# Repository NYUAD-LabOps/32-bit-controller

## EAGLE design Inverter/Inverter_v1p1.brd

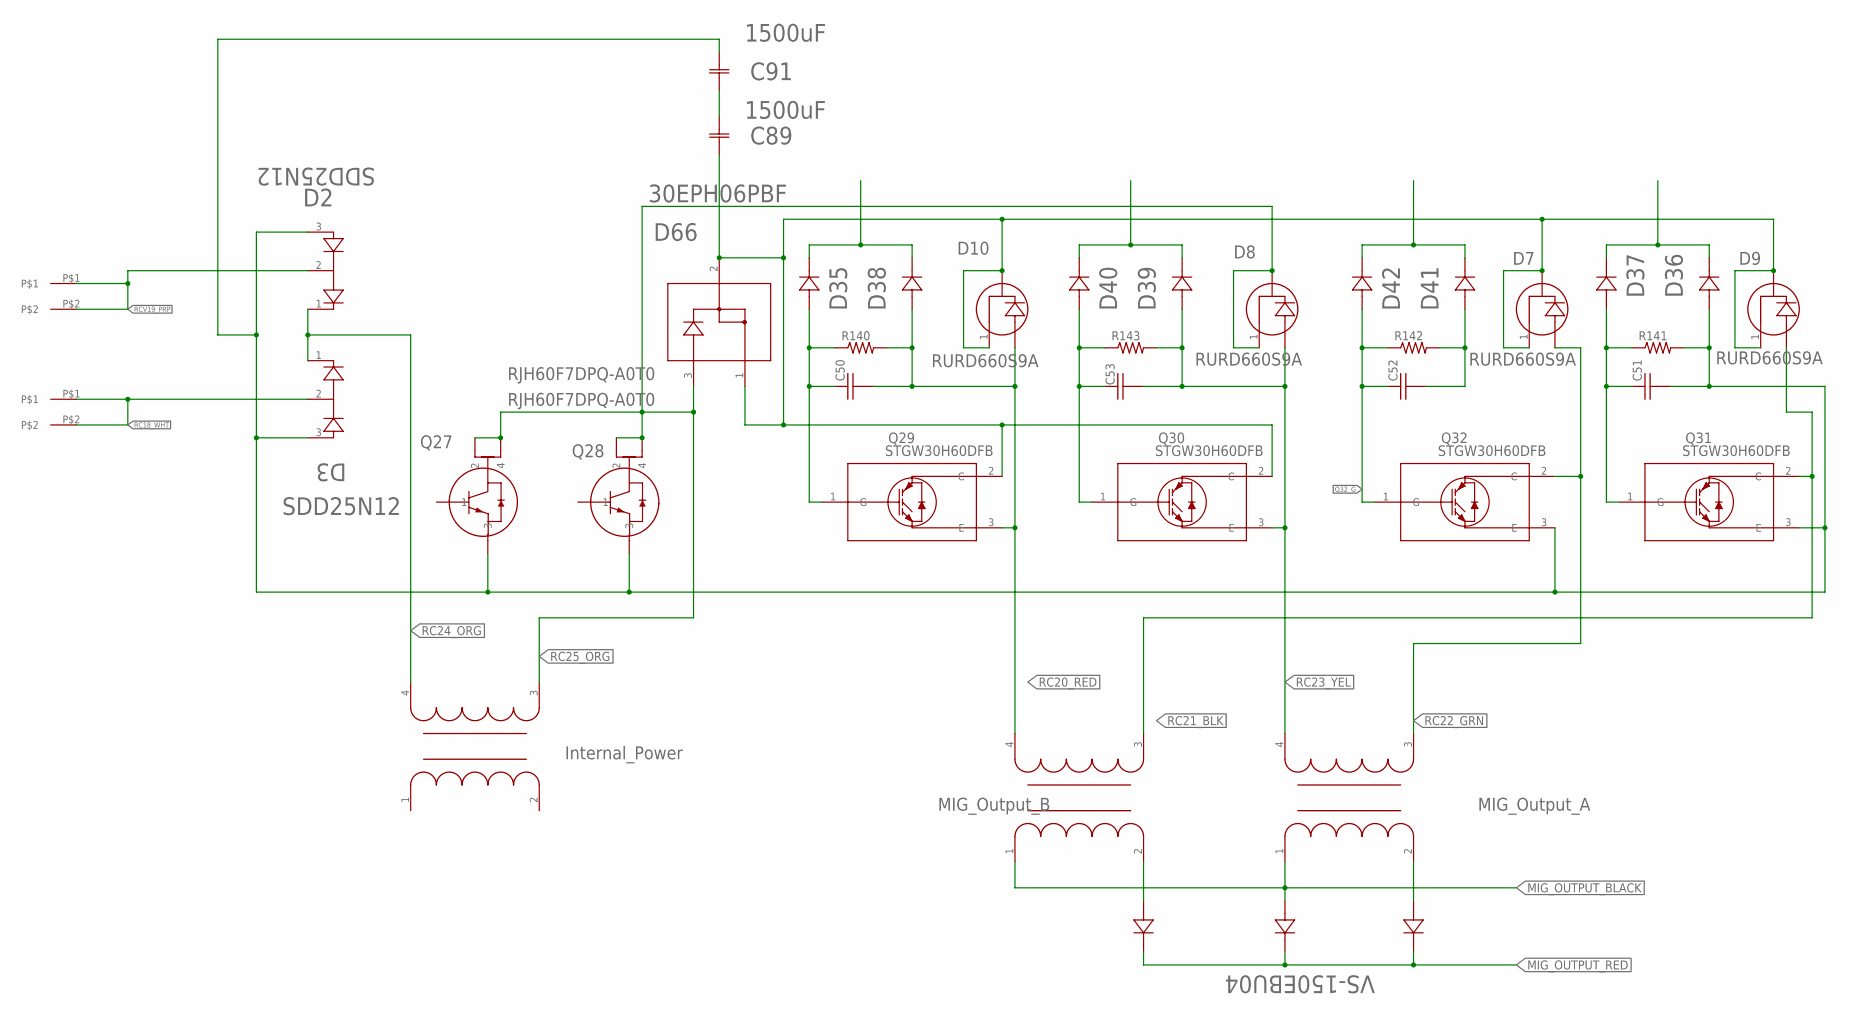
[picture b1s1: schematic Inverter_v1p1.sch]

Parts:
C50, C51, C52, C53: C_0805; 0805
C89, C91: 1500uF; CAP_SLP152M250H9P3_CND
D2, D3: SDD25N12; TO-247AD
D7, D8, D9, D10: RURD660S9A; TO-252
D35, D36, D37, D39, D40, D41, D42: SMAZ18-13-FSMA_DIO-M; SMA_DIO-M
D38: ZJF_638; SMA_DIO-M
D66: 30EPH06PBF; TO-247AC_MOD_VIS
J2, J3: 2-pos; 2_3.81MM_PITCH
Q27, Q28: RJH60F7DPQ-A0T0; TO-247A_REN
Q29, Q30, Q31, Q32: STGW30H60DFB; TO-247_STM
R140, R141, R142, R143: R_0805; 0805
U$1, U$2, U$3: GENERIC_TRANSFORMER
U$4, U$5, U$6: VS-150EBU04; POWER_TAB

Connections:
D66_1: C89.2, D7.1 (C1), D7.3 (C2), D9.1 (C1), D9.3 (C2), D10.1 (C1), D10.3 (C2), D66.1, D66.2, Q29.2 (C), Q30.2 (C)
MIG_OUTPUT_BLACK: U$1.1, U$2.1, U$5.2
MIG_OUTPUT_RED: U$4.1, U$5.1, U$6.1
unnamed: U$1.2, U$4.2
unnamed: C50.1, D35.2, Q29.1 (G), R140.1
unnamed: D39.1, D40.1
unnamed: U$2.2, U$6.2
unnamed: C89.1, C91.2
unnamed: D35.1, D38.1
unnamed: C53.1, D40.2, Q30.1 (G), R143.1
unnamed: C51.1, D37.2, Q31.1 (G), R141.1
unnamed: C52.2, D41.2, R142.2
unnamed: D41.1, D42.1
unnamed: C51.2, C91.1, D2.3, D3.3, D36.2, Q27.3, Q28.3, Q31.3 (E), Q32.3 (E), R141.2
unnamed: D36.1, D37.1
Q32_G: C52.1, D42.2, Q32.1 (G), R142.1
RC18_WHT: D3.2, J3.P$1, J3.P$2
RC20_RED: C50.2, D10.2 (A), D38.2, Q29.3 (E), R140.2, U$1.4
RC21_BLK: D9.2 (A), Q31.2 (C), U$1.3
RC22_GRN: D7.2 (A), Q32.2 (C), U$2.3
RC23_YEL: C53.2, D8.2 (A), D39.2, Q30.3 (E), R143.2, U$2.4
RC24_ORG: D2.1, D3.1, U$3.4
RC25_ORG: D8.1 (C1), D8.3 (C2), D66.3, Q27.2, Q27.4, Q28.2, Q28.4, U$3.3
RCV19_PRP: D2.2, J2.P$1, J2.P$2

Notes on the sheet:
MIG_Output_A
Internal_Power
MIG_Output_B

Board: 2 copper layers, 39 parts (0 on the bottom side), 24 nets, no tracks yet.

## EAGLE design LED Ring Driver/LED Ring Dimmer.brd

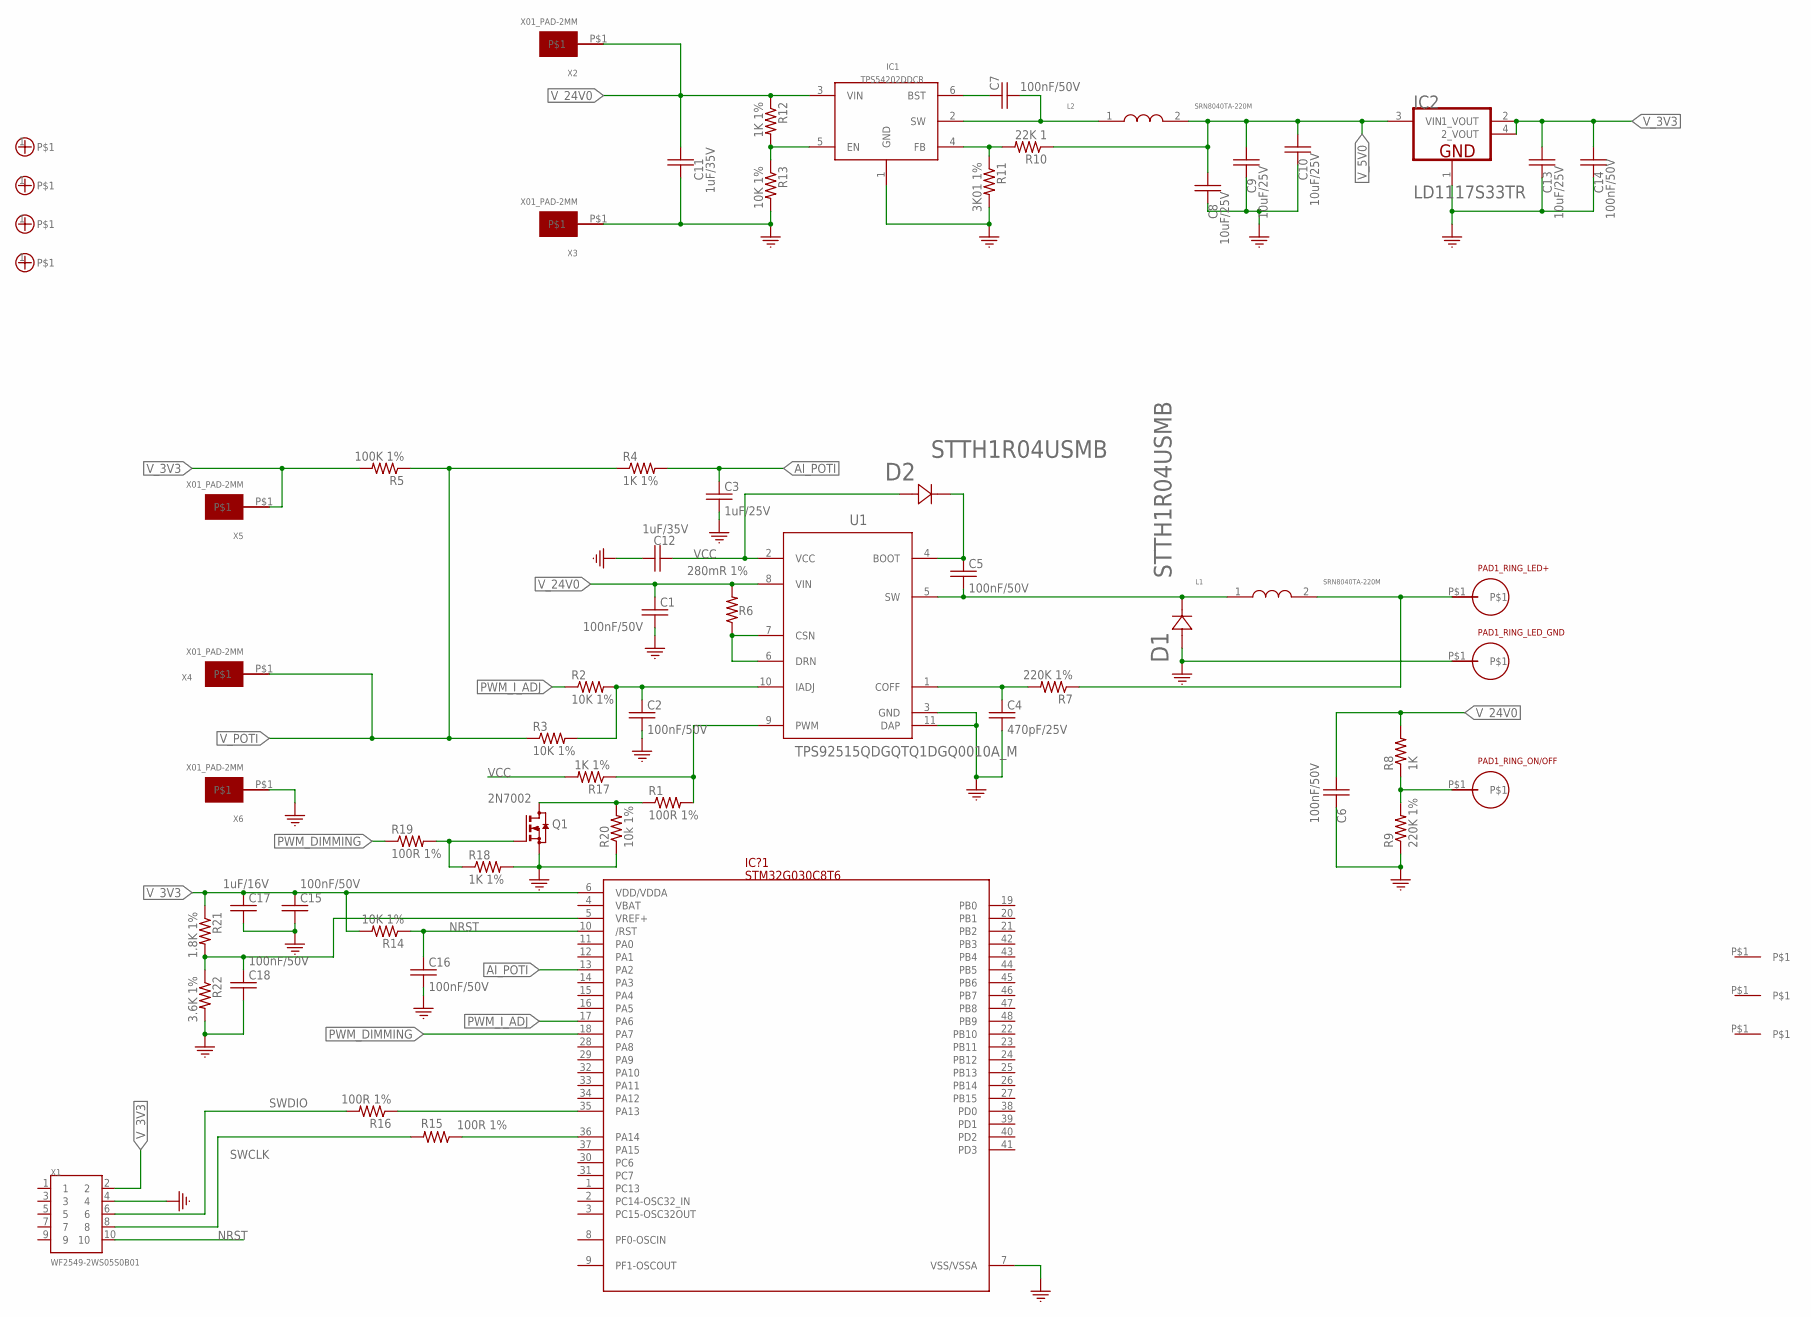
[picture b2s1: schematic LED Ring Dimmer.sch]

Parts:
C1, C2, C5, C6, C7, C14, C15, C16, C18: 100nF/50V; EIA0603
C3: 1uF/25V; EIA0603
C4: 470pF/25V; EIA0603
C8, C9, C10, C13: 10uF/25V; EIA0603
C11, C12: 1uF/35V; EIA0603
C17: 1uF/16V; EIA0603
D1, D2: STTH1R04USMB; SMB
FID1, FID2, FID3: FIDUCIAL
IC1: TPS54202DDCR; SOT23-6
IC2: LD1117S33TR; SOT223_LD1117S33TR
IC?1: STM32G030C8T6; LQFP48
L1, L2: SRN8040TA-220M
M1, M2, M3, M4: M_HOLE_3M; PCB_SCREW_M3_POWER
PAD1_RING_LED+, PAD1_RING_LED_GND, PAD1_RING_ON/OFF: THT_PAD_5MM; THT_PAD_D5.0
Q1: 2N7002; SOT23
R1, R15, R16, R19: 100R 1%; EIA0603
R2, R3, R13, R14: 10K 1%; EIA0603
R4, R12, R17, R18: 1K 1%; EIA0603
R5: 100K 1%; EIA0603
R6: 280mR 1%; EIA1206
R7, R9: 220K 1%; EIA0603
R8: 1K; EIA0603
R10: 22K 1; EIA0603
R11: 3K01 1%; EIA0603
R20: 10k 1%; EIA0603
R21: 1.8K 1%; EIA0603
R22: 3.6K 1%; EIA0603
U1: TPS92515QDGQTQ1DGQ0010A_M; DGQ0010A_M
X1: WF2549-2WS05S0B01; X10_100MIL_2XROW_VERT
X2, X3, X4, X5, X6: X01_PAD-2MM

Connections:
AI_POTI: C3.1, IC?1.13 (PA2), R4.2
GND: C1.2, C2.2, C3.2, C4.2, C6.2, C8.2, C9.2, C10.2, C11.2, C12.1, C13.2, C14.2, C15.2, C16.2, C17.2, C18.2, D1.A, IC1.1 (GND), IC2.1 (GND), IC?1.7 (VSS/VSSA), PAD1_RING_LED_GND.P$1, Q1.2 (S), R9.1, R11.2, R13.2, R18.2, R20.1, R22.2, U1.3 (GND), U1.11 (DAP), X1.4, X3.P$1, X6.P$1
unnamed: C1.1, R6.2, U1.8 (VIN)
unnamed: C5.2, D1.K (C), L1.1, U1.5 (SW)
unnamed: R6.1, U1.6 (DRN), U1.7 (CSN)
unnamed: C2.1, R2.2, R3.2, U1.10 (IADJ)
unnamed: C4.1, R7.2, U1.1 (COFF)
unnamed: R1.2, R17.1, U1.9 (PWM)
unnamed: L1.2, PAD1_RING_LED+.P$1, R7.1
unnamed: C5.1, D2.K (C), U1.4 (BOOT)
unnamed: PAD1_RING_ON/OFF.P$1, R8.1, R9.2
unnamed: C7.1, IC1.6 (BST)
unnamed: C7.2, IC1.2 (SW), L2.1
unnamed: IC1.4 (FB), R10.2, R11.1
unnamed: Q1.3 (D), R1.1, R20.2
unnamed: IC1.5 (EN), R12.2, R13.1
unnamed: Q1.1 (G), R18.1, R19.2
unnamed: C18.1, IC?1.5 (VREF+), R21.2, R22.1
unnamed: IC?1.35 (PA13), R16.1
unnamed: IC?1.36 (PA14), R15.1
NRST: C16.1, IC?1.10 (/RST), R14.1, X1.10
PWM_DIMMING: IC?1.18 (PA7), R19.1
PWM_I_ADJ: IC?1.17 (PA6), R2.1
SWCLK: R15.2, X1.8
SWDIO: R16.2, X1.6
VCC: C12.2, D2.A, R17.2, U1.2 (VCC)
V_3V3: C13.1, C14.1, C15.1, C17.1, IC2.2 (1_VOUT), IC2.4 (2_VOUT), IC?1.6 (VDD/VDDA), R5.2, R14.2, R21.1, X1.2, X5.P$1
V_5V0: C8.1, C9.1, C10.1, IC2.3 (VIN), L2.2, R10.1
V_24V0: C6.1, C11.1, IC1.3 (VIN), R8.2, R12.1, X2.P$1
V_POTI: R3.1, R4.1, R5.1, X4.P$1

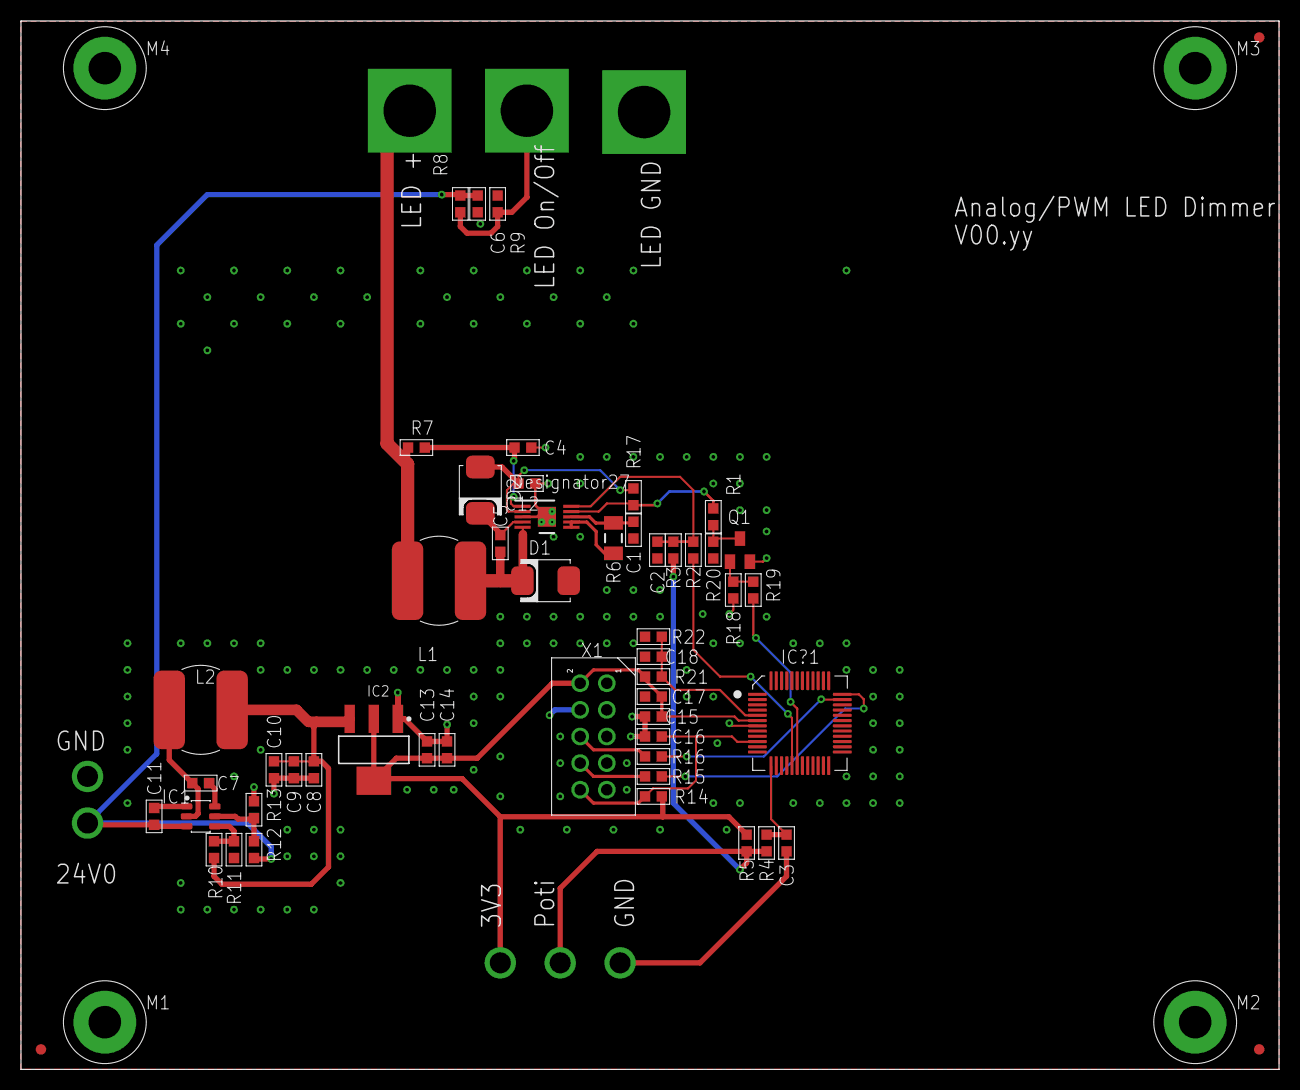
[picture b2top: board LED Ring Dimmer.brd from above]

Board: 2 copper layers, 120.0 x 100.0 mm, 65 parts (0 on the bottom side), 30 nets.

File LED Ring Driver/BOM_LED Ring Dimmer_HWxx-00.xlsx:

Qty | Value | Device | Package | Parts | DESCRIPTION | MFN | MFR | PART_VALUE
1 |  | C_0603EIA0603 | EIA0603 | C3
3 |  | R_0603 | EIA0603 | R2, R3, R7 |  | Open Source 0603
1 | 1.8K 1% | R_0603 | EIA0603 | R21 |  | Open Source 0603
1 | 100K 1% | R_0603 | EIA0603 | R5 |  | Open Source 0603
4 | 100R 1% | R_0603 | EIA0603 | R1, R15, R16, R19 |  | Open Source 0603
10 | 100nF/50V | C_0603EIA0603 | EIA0603 | C1, C2, C4, C5, C6, C7, C14, C15, C16, C18
2 | 10K 1% | R_0603 | EIA0603 | R13, R14 |  | Open Source 0603
1 | 10k 1% | R_0603 | EIA0603 | R20 |  | Open Source 0603
4 | 10uF/25V | C_0603EIA0603 | EIA0603 | C8, C9, C10, C13
1 | 1K | R_0603 | EIA0603 | R8 |  | Open Source 0603
4 | 1K 1% | R_0603 | EIA0603 | R4, R12, R17, R18 |  | Open Source 0603
1 | 1uF/16V | C_0603EIA0603 | EIA0603 | C17
2 | 1uF/35V | C_0603EIA0603 | EIA0603 | C11, C12
1 | 220K 1% | R_0603 | EIA0603 | R9 |  | Open Source 0603
1 | 22K 1 | R_0603 | EIA0603 | R10 |  | Open Source 0603
1 | 280mR 1% | R_1206EIA1206 | EIA1206 | R6 |  | Open Source R1206
1 | 2N7002 | 2N7002 | SOT23 | Q1 | NMOSFET, 500mA, 60V, Vth 2.5V | 2N7002 | Diodes, Guangdong Hotetech,NXP | NMOSFET
1 | 3.6K 1% | R_0603 | EIA0603 | R22 |  | Open Source 0603
1 | 3K01 1% | R_0603 | EIA0603 | R11 |  | Open Source 0603
3 | FIDUCIAL | FIDUCIAL | FIDUCIAL | FID1, FID2, FID3
1 | LD1117S33TR | LD1117S33TR | SOT223_LD1117S33TR | IC2 | LDO,Fixed 15V 3.3V 1.3V @ 800mA SOT-223 | LD1117S33TR | STmicro, Diodes, TI, | xx1117x33xx
4 | M_HOLE_3M | M_HOLE_3M | PCB_SCREW_M3_POWER | M1, M2, M3, M4
2 | SRN8040TA-220M | SRN8040TA-220M | SRN8040TA-220M | L1, L2 | FIXED IND 22UH 2.9A SMD, 73m-Ohm, Bourns | SRN8040TA-220M | Bourns | 22uH/2.9A
1 | STM32G030C8T6 | STM32G030C8T6 | LQFP48 | IC?1
2 | STTH1R04USMB | STTH1R04USMB | SMB | D1, D2 | 1A, 400V, SMB, Fast Recovery | STTH1R04U |  | STTH1R04U
3 | THT_PAD_5MM | THT_PAD_5MM | THT_PAD_D5.0 | PAD1_RING_LED+, PAD1_RING_LED_GND, PAD1_RING_ON/OFF
1 | TPS54202DDCR | TPS54202DDCR | SOT23-6 | IC1 | 2A 28V SOT-23-6 Sync Buck | TPS54202DDCR | Texas Instruments | TPS54202
1 | TPS92515QDGQTQ1DGQ0010A_M | TPS92515QDGQTQ1DGQ0010A_M | DGQ0010A_M | U1 | LED Driver 2A, 42V, Buck, Analog and PWM Dimming,MSOP-PowerPad-10 | TPS92515QDGQTQ1 | Texas Instruments | TPS92515
1 | WF2549-2WS05S0B01 | WF2549-2WS05S0B01 | X10_100MIL_2XROW_VERT | X1 | X10, 10 Pins, Header, Pitch 2.54 wire to board 2xrows, THT | WF2549-2WS05S0B01 | WCON
5 | X01_PAD-2MM | X01_PAD-2MM | X01_PAD-2MM | X2, X3, X4, X5, X6

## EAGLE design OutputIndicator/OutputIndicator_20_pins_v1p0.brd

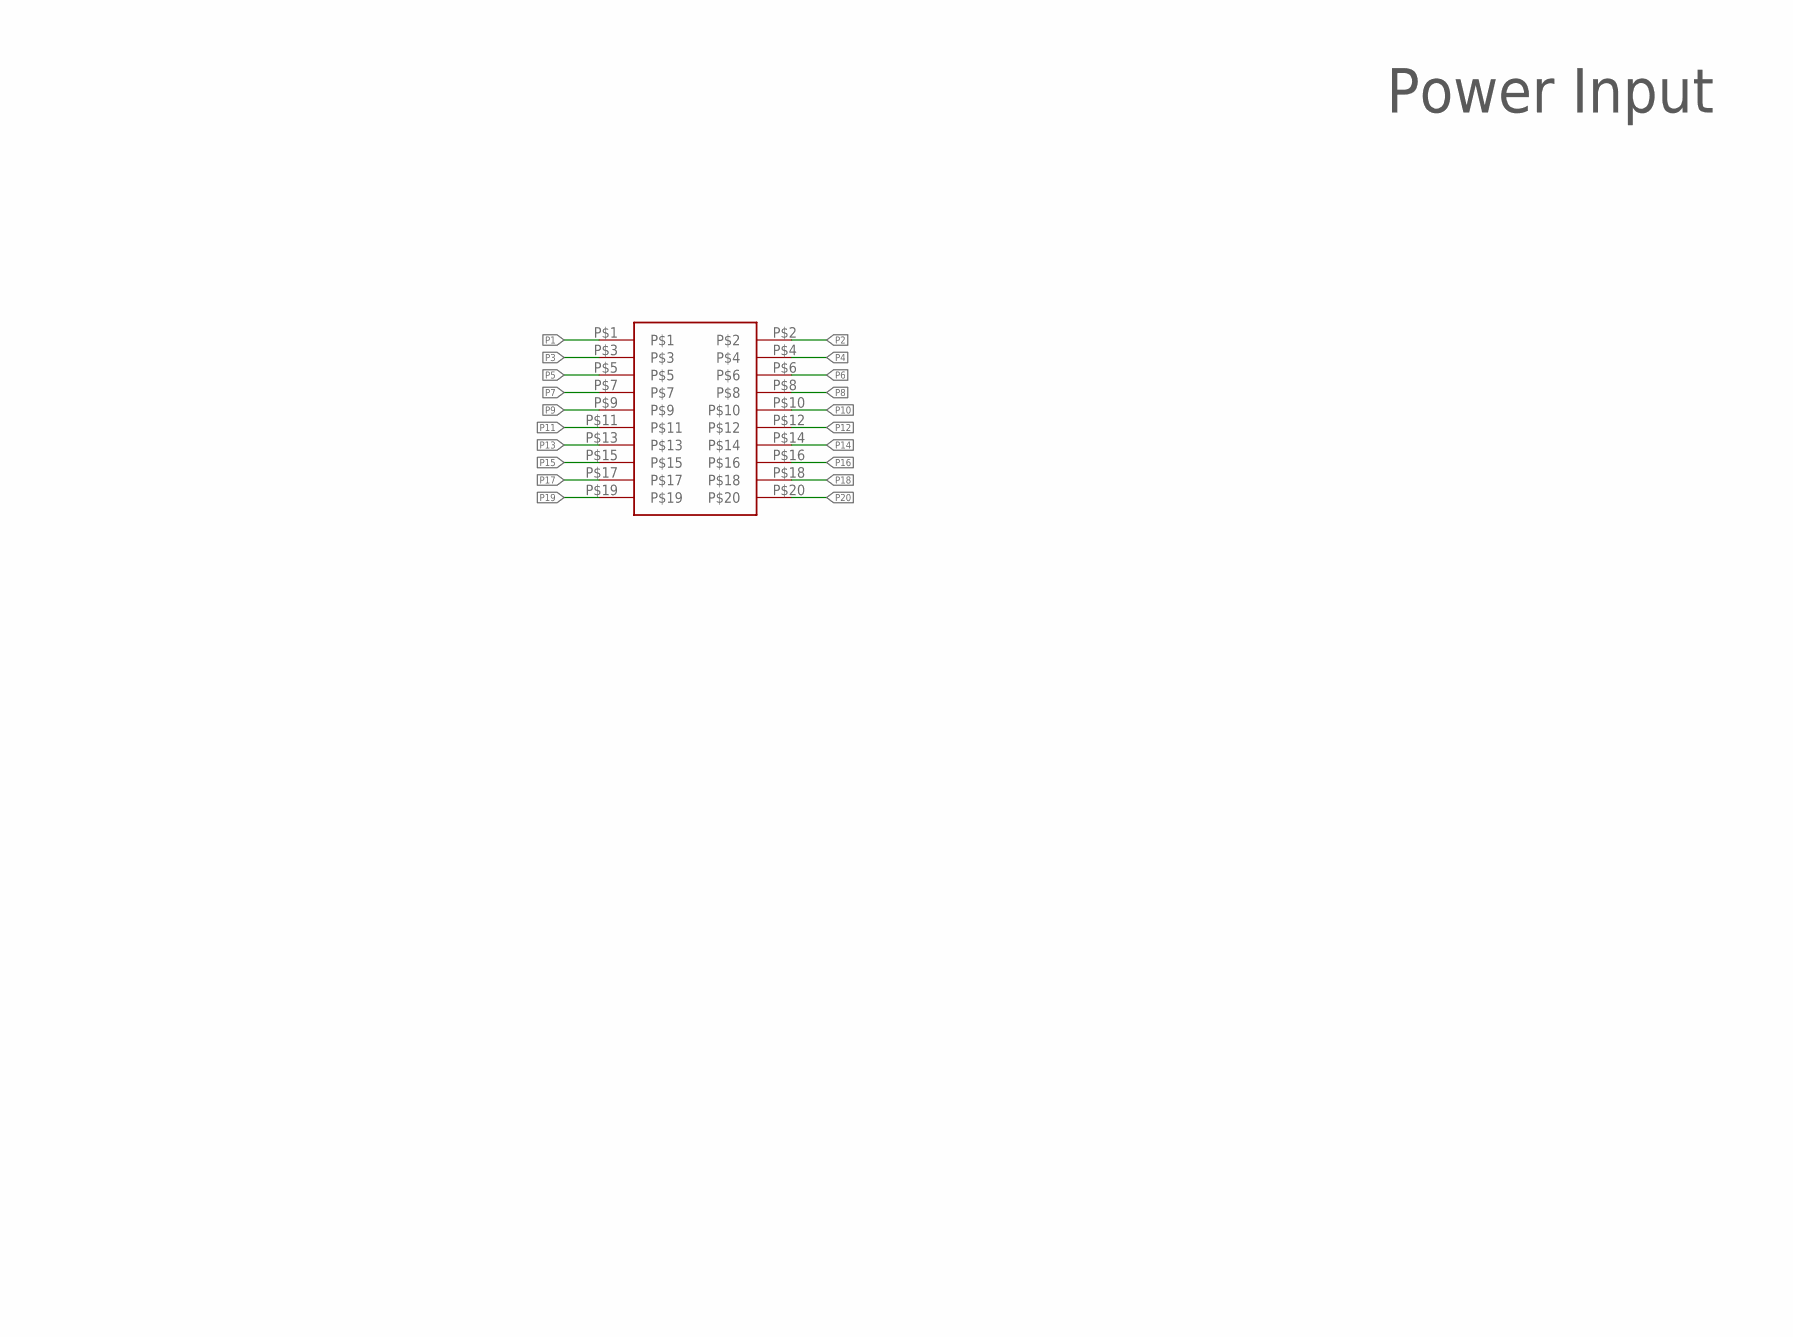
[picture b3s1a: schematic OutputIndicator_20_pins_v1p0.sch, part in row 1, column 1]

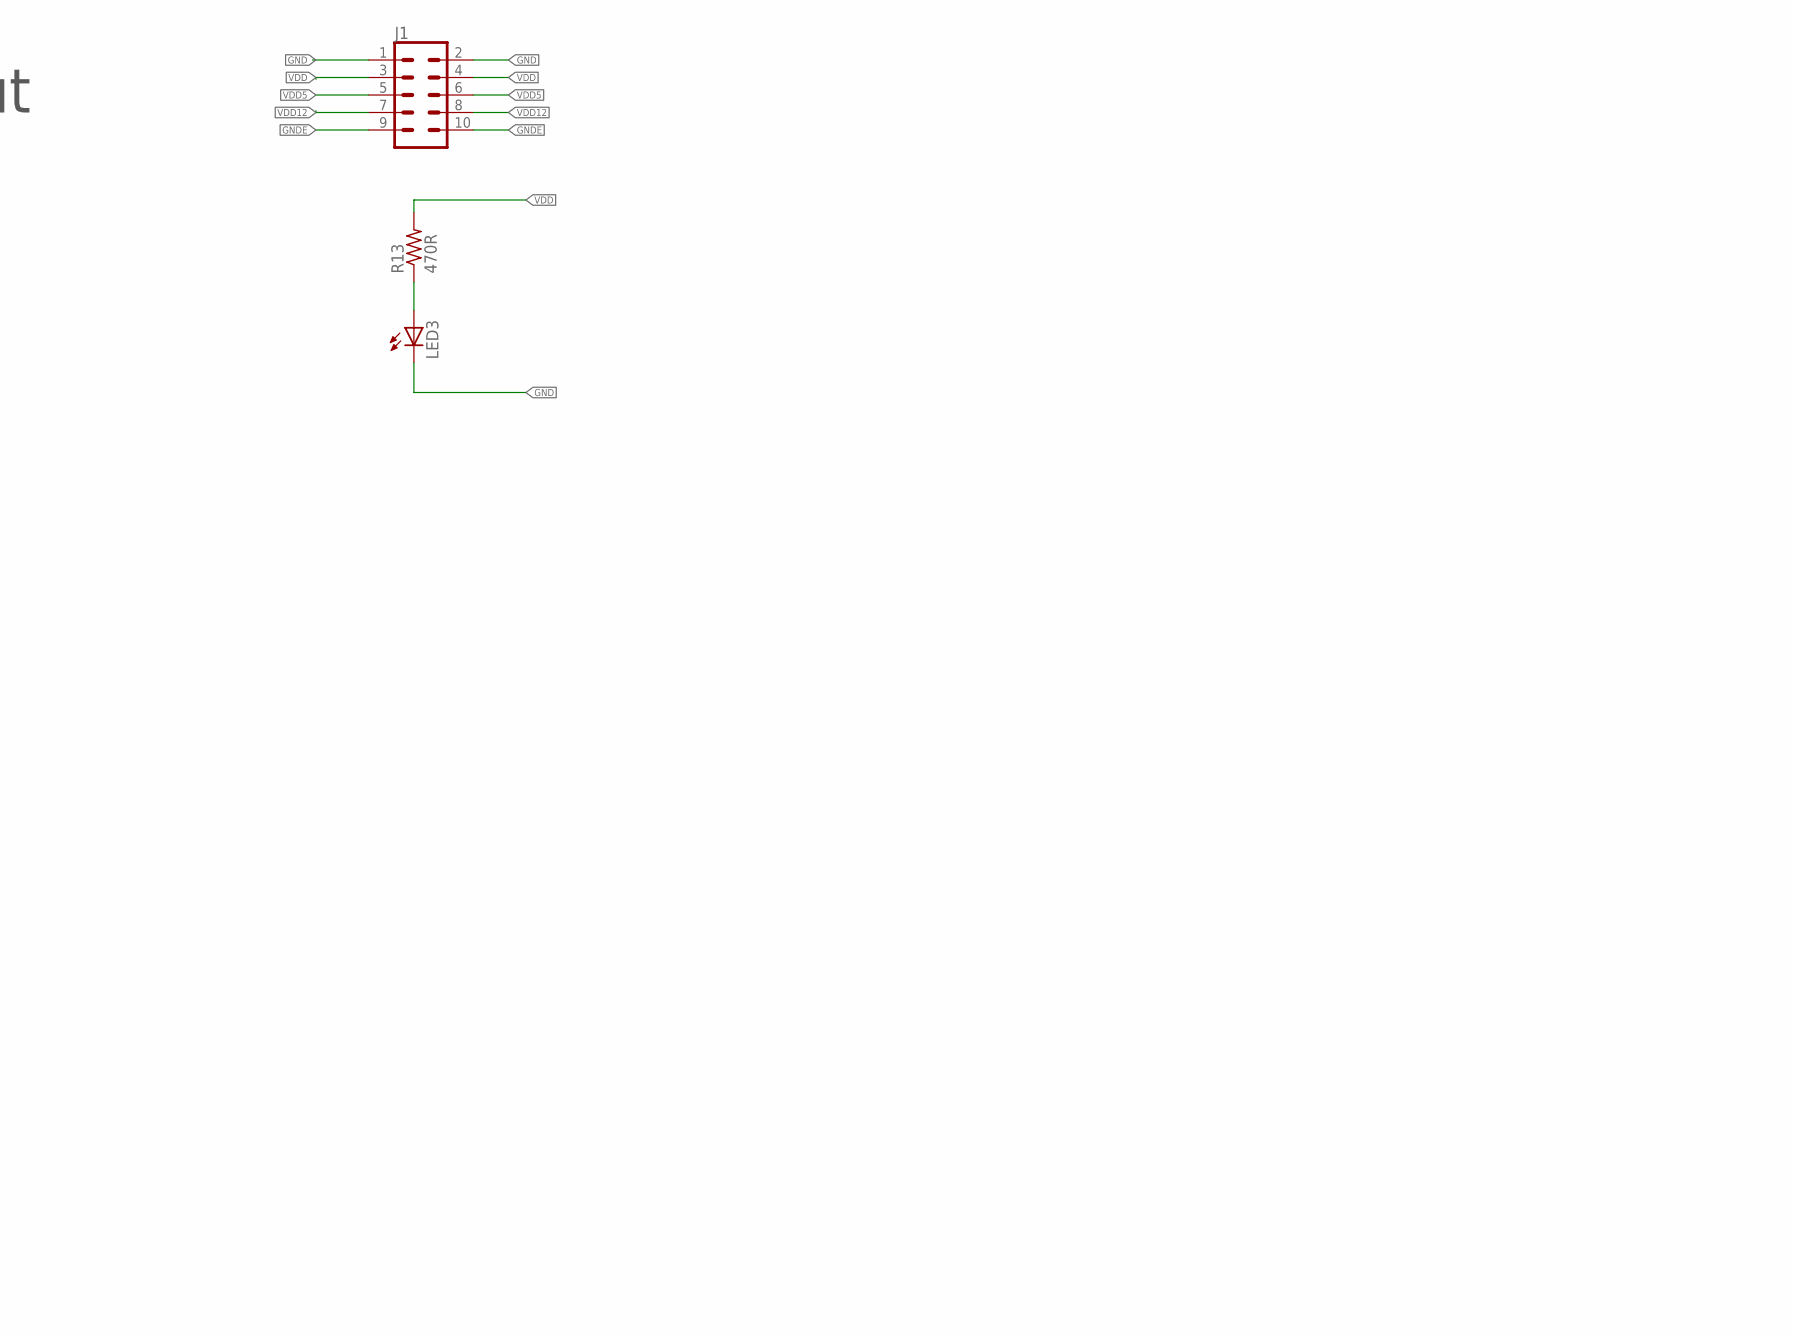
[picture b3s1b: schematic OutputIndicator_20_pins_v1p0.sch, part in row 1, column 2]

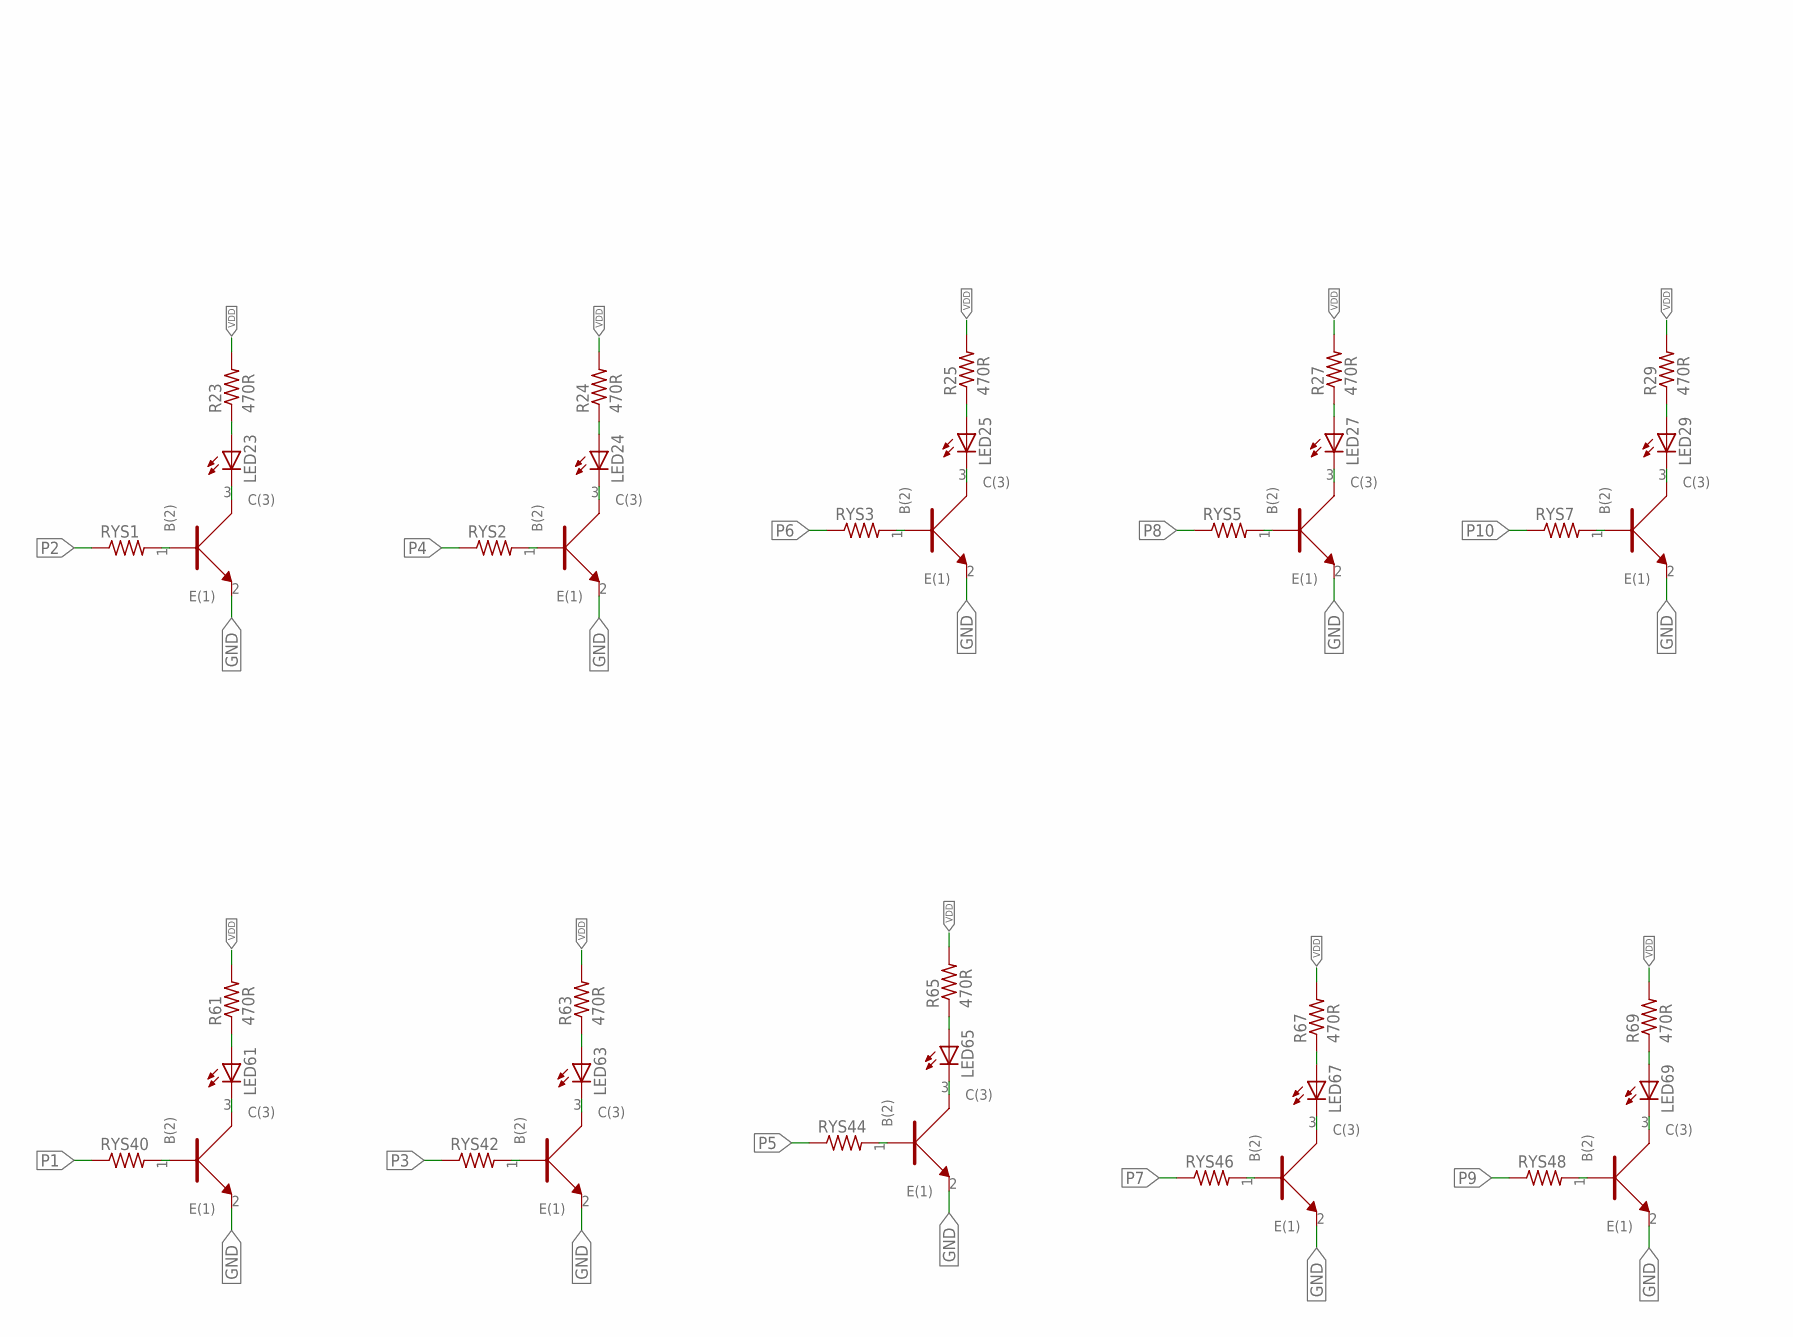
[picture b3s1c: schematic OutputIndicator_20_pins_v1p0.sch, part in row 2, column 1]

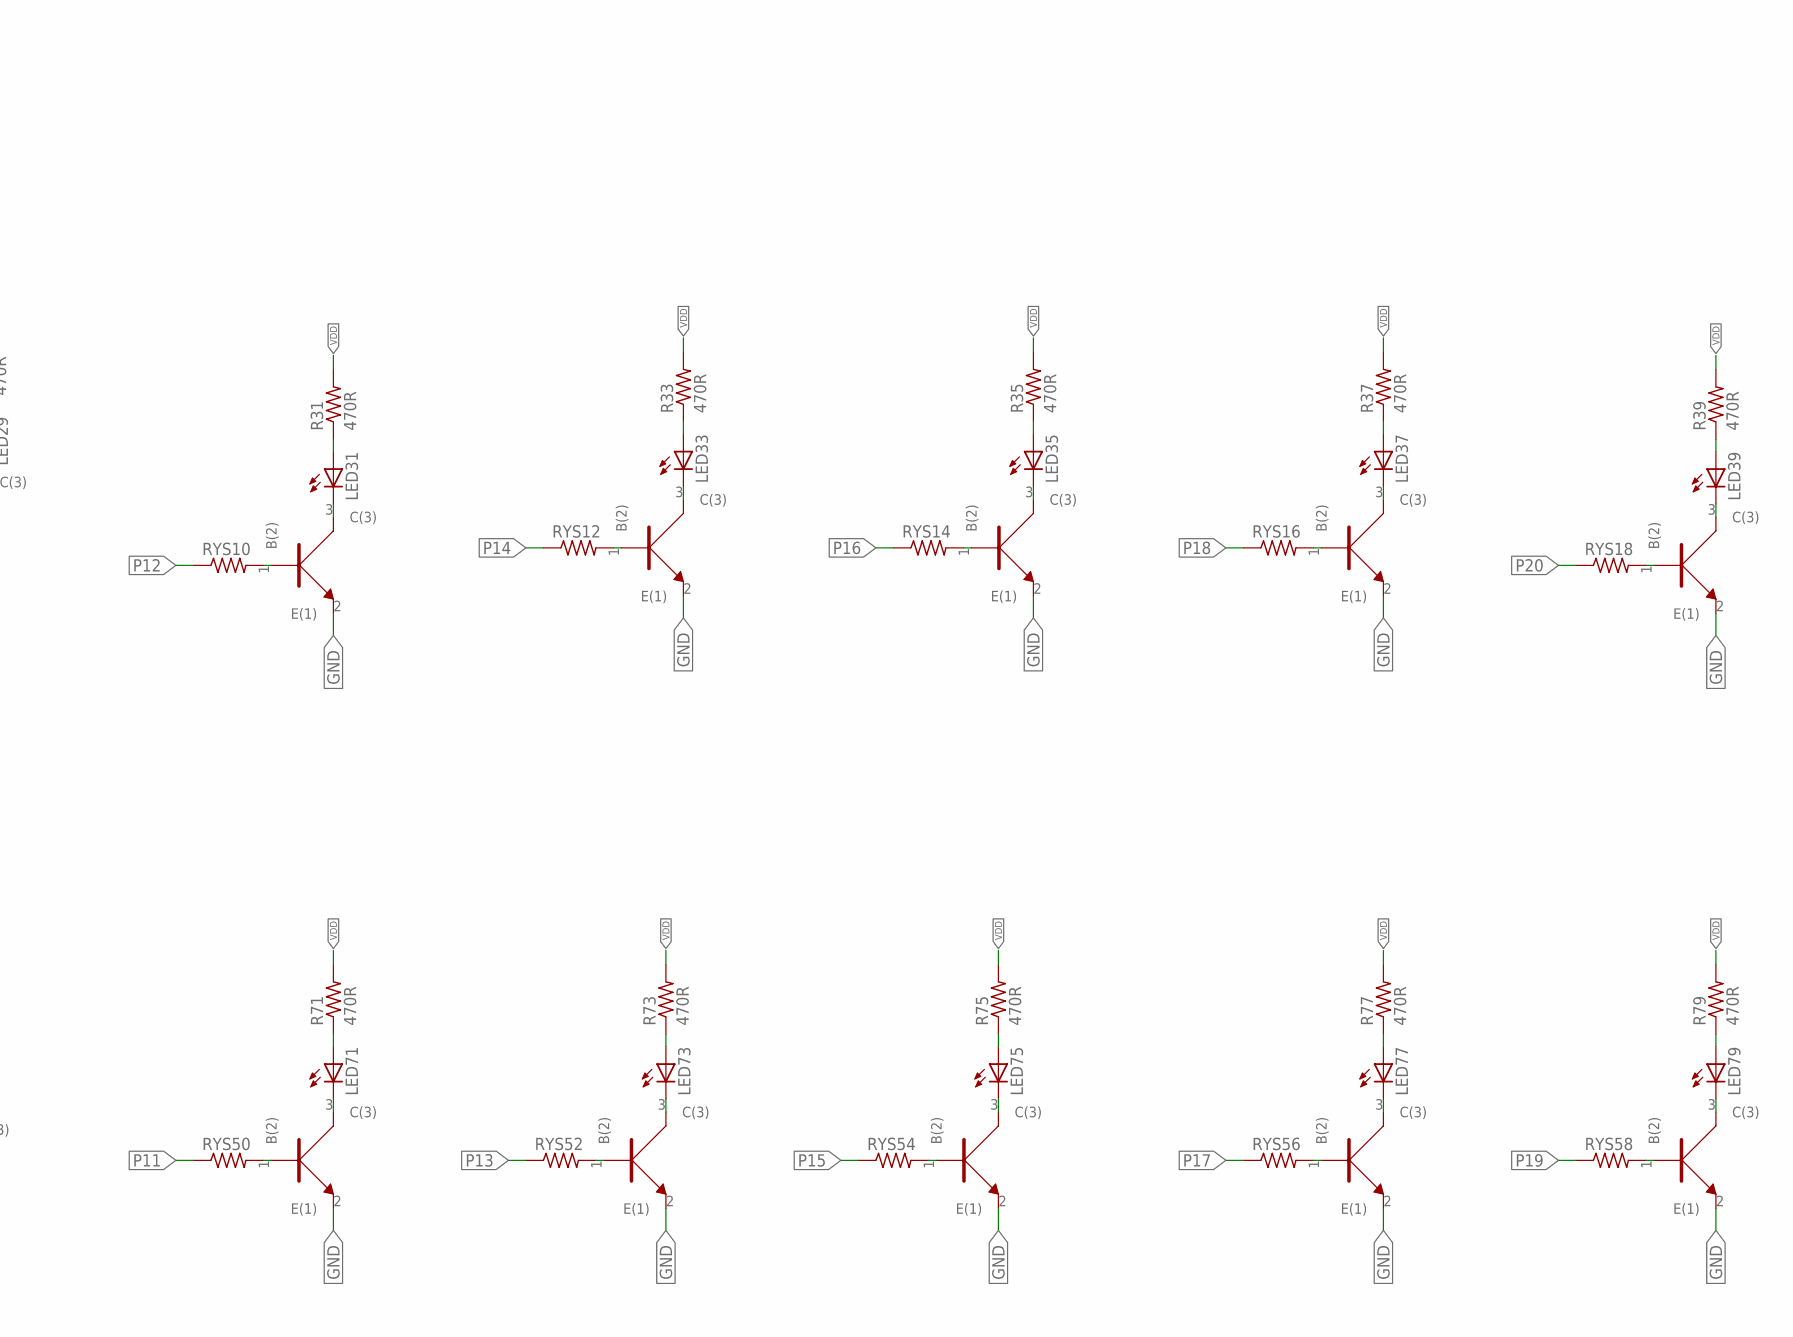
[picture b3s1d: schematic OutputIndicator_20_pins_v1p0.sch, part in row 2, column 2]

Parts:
J1: CONN_05X2PTH; 2X5
J2: 2_X_10_HEADER_GENERIC; 2_X_10_.1_INCH
LED3, LED23, LED24, LED25, LED27, LED29, LED31, LED33, LED35, LED37, LED39, LED61, LED63, LED65, LED67, LED69, LED71, LED73, LED75, LED77, LED79: LED_0805_GREEN
R13, R23, R24, R25, R27, R29, R31, R33, R35, R37, R39, R61, R63, R65, R67, R69, R71, R73, R75, R77, R79: 470R; 0402
RYS1, RYS2, RYS3, RYS5, RYS7, RYS10, RYS12, RYS14, RYS16, RYS18, RYS40, RYS42, RYS44, RYS46, RYS48, RYS50, RYS52, RYS54, RYS56, RYS58: 1K; 0402
U1, U2, U3, U5, U7, U9, U11, U13, U15, U17, U40, U42, U44, U46, U48, U50, U52, U54, U56, U58: BC846BW; SOT323

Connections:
GND: J1.1, J1.2, LED3.C, U1.2 (E(1)), U2.2 (E(1)), U3.2 (E(1)), U5.2 (E(1)), U7.2 (E(1)), U9.2 (E(1)), U11.2 (E(1)), U13.2 (E(1)), U15.2 (E(1)), U17.2 (E(1)), U40.2 (E(1)), U42.2 (E(1)), U44.2 (E(1)), U46.2 (E(1)), U48.2 (E(1)), U50.2 (E(1)), U52.2 (E(1)), U54.2 (E(1)), U56.2 (E(1)), U58.2 (E(1))
GNDE: J1.9, J1.10
unnamed: LED3.A, R13.P$1 (1)
unnamed: RYS1.P$2 (2), U1.1 (B(2))
unnamed: LED23.A, R23.P$1 (1)
unnamed: LED23.C, U1.3 (C(3))
unnamed: RYS2.P$2 (2), U2.1 (B(2))
unnamed: LED24.A, R24.P$1 (1)
unnamed: LED24.C, U2.3 (C(3))
unnamed: RYS3.P$2 (2), U3.1 (B(2))
unnamed: LED25.A, R25.P$1 (1)
unnamed: LED25.C, U3.3 (C(3))
unnamed: RYS5.P$2 (2), U5.1 (B(2))
unnamed: LED27.A, R27.P$1 (1)
unnamed: LED27.C, U5.3 (C(3))
unnamed: RYS7.P$2 (2), U7.1 (B(2))
unnamed: LED29.A, R29.P$1 (1)
unnamed: LED29.C, U7.3 (C(3))
unnamed: RYS10.P$2 (2), U9.1 (B(2))
unnamed: LED31.A, R31.P$1 (1)
unnamed: LED31.C, U9.3 (C(3))
unnamed: RYS12.P$2 (2), U11.1 (B(2))
unnamed: LED33.A, R33.P$1 (1)
unnamed: LED33.C, U11.3 (C(3))
unnamed: RYS14.P$2 (2), U13.1 (B(2))
unnamed: LED35.A, R35.P$1 (1)
unnamed: LED35.C, U13.3 (C(3))
unnamed: RYS16.P$2 (2), U15.1 (B(2))
unnamed: LED37.A, R37.P$1 (1)
unnamed: LED37.C, U15.3 (C(3))
unnamed: RYS18.P$2 (2), U17.1 (B(2))
unnamed: LED39.A, R39.P$1 (1)
unnamed: LED39.C, U17.3 (C(3))
unnamed: RYS40.P$2 (2), U40.1 (B(2))
unnamed: LED61.A, R61.P$1 (1)
unnamed: LED61.C, U40.3 (C(3))
unnamed: RYS42.P$2 (2), U42.1 (B(2))
unnamed: LED63.A, R63.P$1 (1)
unnamed: LED63.C, U42.3 (C(3))
unnamed: RYS44.P$2 (2), U44.1 (B(2))
unnamed: LED65.A, R65.P$1 (1)
unnamed: LED65.C, U44.3 (C(3))
unnamed: RYS46.P$2 (2), U46.1 (B(2))
unnamed: LED67.A, R67.P$1 (1)
unnamed: LED67.C, U46.3 (C(3))
unnamed: RYS48.P$2 (2), U48.1 (B(2))
unnamed: LED69.A, R69.P$1 (1)
unnamed: LED69.C, U48.3 (C(3))
unnamed: RYS50.P$2 (2), U50.1 (B(2))
unnamed: LED71.A, R71.P$1 (1)
unnamed: LED71.C, U50.3 (C(3))
unnamed: RYS52.P$2 (2), U52.1 (B(2))
unnamed: LED73.A, R73.P$1 (1)
unnamed: LED73.C, U52.3 (C(3))
unnamed: RYS54.P$2 (2), U54.1 (B(2))
unnamed: LED75.A, R75.P$1 (1)
unnamed: LED75.C, U54.3 (C(3))
unnamed: RYS56.P$2 (2), U56.1 (B(2))
unnamed: LED77.A, R77.P$1 (1)
unnamed: LED77.C, U56.3 (C(3))
unnamed: RYS58.P$2 (2), U58.1 (B(2))
unnamed: LED79.A, R79.P$1 (1)
unnamed: LED79.C, U58.3 (C(3))
P1: J2.P$1, RYS40.P$1 (1)
P2: J2.P$2, RYS1.P$1 (1)
P3: J2.P$3, RYS42.P$1 (1)
P4: J2.P$4, RYS2.P$1 (1)
P5: J2.P$5, RYS44.P$1 (1)
P6: J2.P$6, RYS3.P$1 (1)
P7: J2.P$7, RYS46.P$1 (1)
P8: J2.P$8, RYS5.P$1 (1)
P9: J2.P$9, RYS48.P$1 (1)
P10: J2.P$10, RYS7.P$1 (1)
P11: J2.P$11, RYS50.P$1 (1)
P12: J2.P$12, RYS10.P$1 (1)
P13: J2.P$13, RYS52.P$1 (1)
P14: J2.P$14, RYS12.P$1 (1)
P15: J2.P$15, RYS54.P$1 (1)
P16: J2.P$16, RYS14.P$1 (1)
P17: J2.P$17, RYS56.P$1 (1)
P18: J2.P$18, RYS16.P$1 (1)
P19: J2.P$19, RYS58.P$1 (1)
P20: J2.P$20, RYS18.P$1 (1)
VDD: J1.3, J1.4, R13.P$2 (2), R23.P$2 (2), R24.P$2 (2), R25.P$2 (2), R27.P$2 (2), R29.P$2 (2), R31.P$2 (2), R33.P$2 (2), R35.P$2 (2), R37.P$2 (2), R39.P$2 (2), R61.P$2 (2), R63.P$2 (2), R65.P$2 (2), R67.P$2 (2), R69.P$2 (2), R71.P$2 (2), R73.P$2 (2), R75.P$2 (2), R77.P$2 (2), R79.P$2 (2)
VDD5: J1.5, J1.6
VDD12: J1.7, J1.8

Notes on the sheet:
Power Input

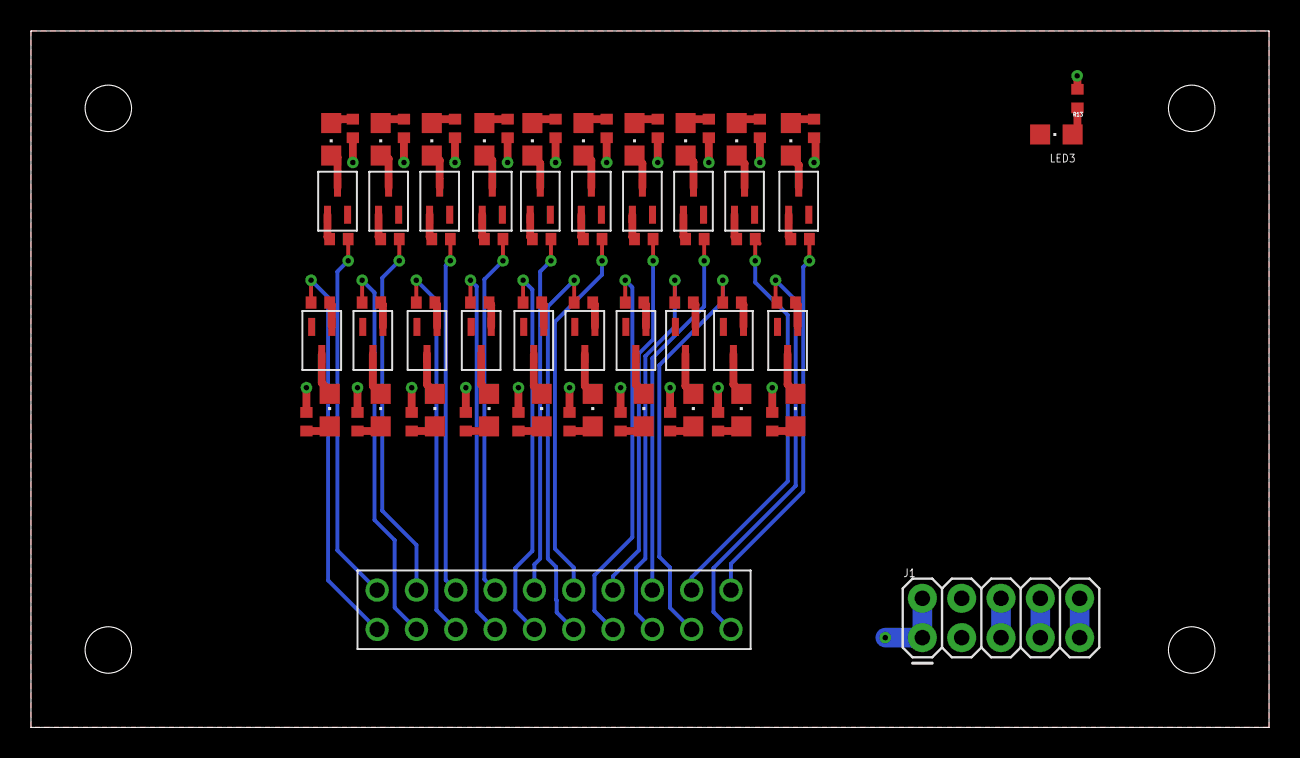
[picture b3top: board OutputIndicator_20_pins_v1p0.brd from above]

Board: 2 copper layers, 80.0 x 45.0 mm, 84 parts (0 on the bottom side), 86 nets.

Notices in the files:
parts and their libraries:
COPYRIGHT: Copyright (C) 2018 Accelerated Designs. All rights reserved
Labops_Lib_AH: COPYRIGHT: Copyright (C) 2023 Ultra Librarian. All rights reserved.
